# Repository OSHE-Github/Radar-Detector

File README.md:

# Radar-Detector

## Project Details
#### a fully open-source radar detector that can be easily replicated by others. Unlike existing commercial solutions, which are proprietary, this design will provide transparency, customization, and accessibility to users. By creating the first truly open-source radar detector, the project expands available options for individuals interested in building, modifying, or better understanding radar detection technology.
#### This device is powered by the 12V port that's in every commercial vehicle by using a 5V adapter and USB-C connector on board.

## Current State
#### The current Design includes
#### - Completed RF and Control Board
#### - Completed Antenna and Waveguide
#### - A breadboarded circuit for K band detection

## Semester End Report
#### For the Enterprise Program at Michigan Tech there is a end of semester report for the project to summarize the progress of the project. [Link](https://docs.google.com/document/d/1saLg0oObQiK9GF-1CGu6zWZuvDCvK0RMIuFfh2jqqCw/edit?usp=sharing)

## Relevant Standards
#### - Traces Were sized appropriately for current being drawn
#### - No traces can be ran under the main RF lines
#### - There was fusing put in front of the main power input from the USB-C
#### - Decoupling capacitors used to reduce noise from voltage sources going into sensitive components

## Constraints of Design
#### - when working with high frequencies up to 40GHz you have to use special small components that can handle it
#### - The material to make a PCB that can handle that high of frequencies is very expensive
#### - Amplifiers for this frequency are very expensive

## Next Semester Goals
#### - Look into possible cheaper solutions using modules like what we found for the K band
#### - Test the Ka band implementation once we have the antenna
#### - Look into the design on the component for the K band and see if parts of it are re-creatable

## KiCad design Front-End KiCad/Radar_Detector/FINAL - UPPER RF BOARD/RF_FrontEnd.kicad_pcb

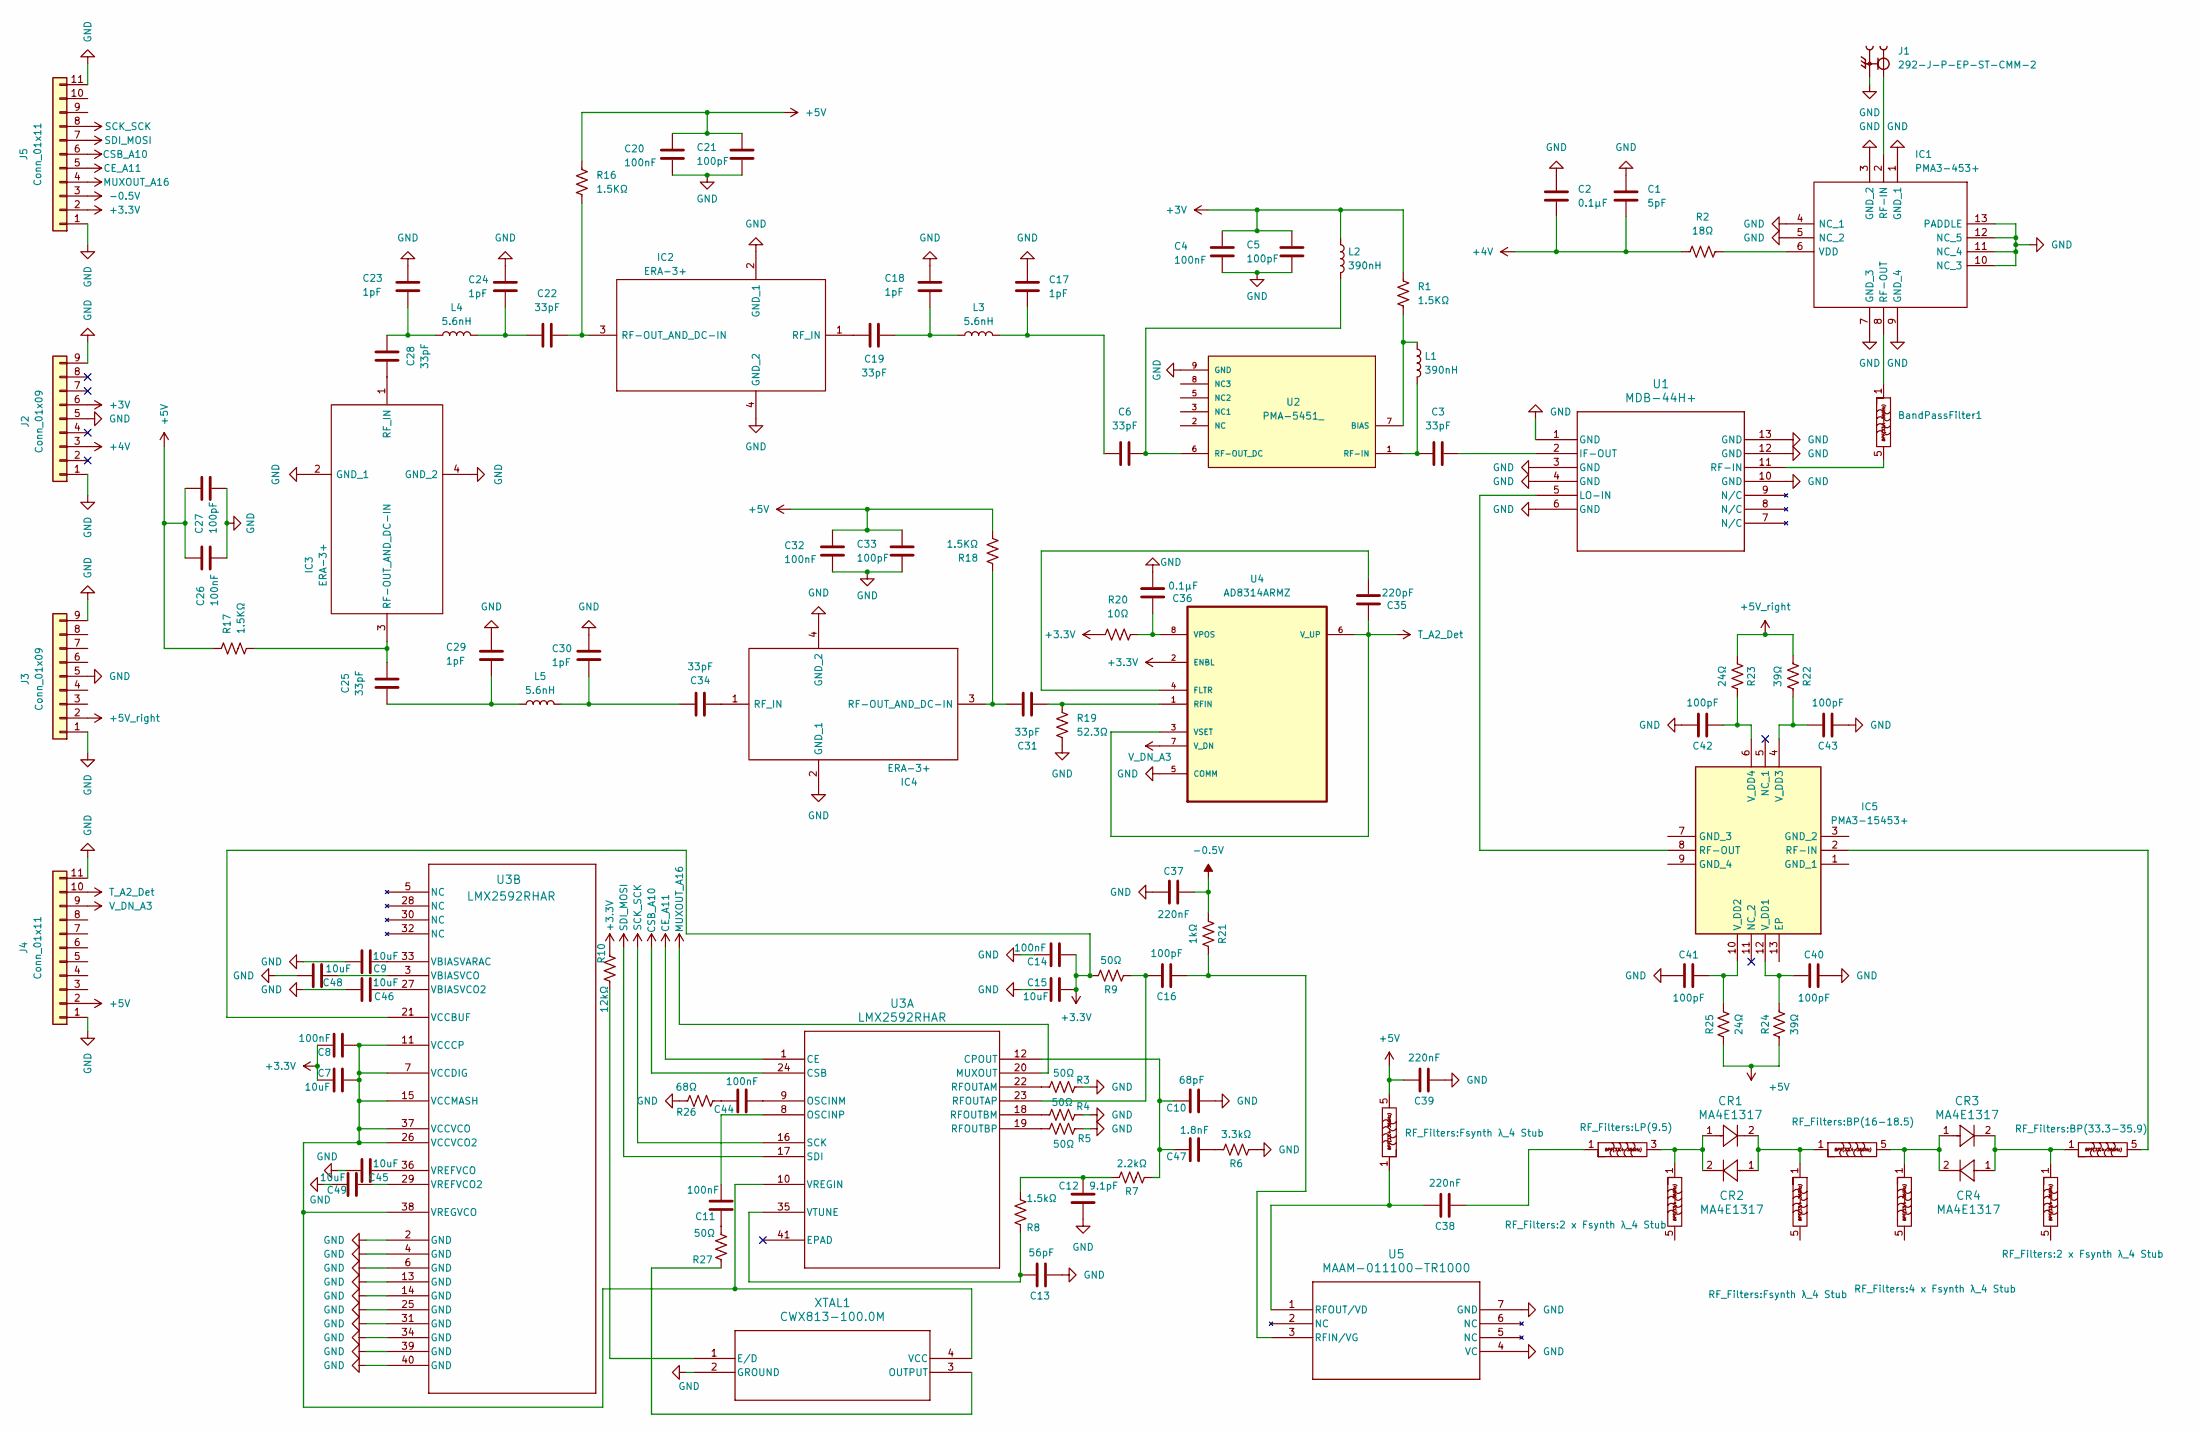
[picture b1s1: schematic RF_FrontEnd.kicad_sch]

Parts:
BandPassFilter1: BP(33.4-36)
BandPassFilter2: 16-18.5 GHz; BP(16-18.5)
BandPassFilter3: 33.3-35.9 GHz; BP(33.3-35.9)
BandPassFilter4: 16-18.5 GHz; LP(9.5)
BandPassFilter5, BandPassFilter7: 16-18.5 GHz; Fsynth λ_4 Stub
BandPassFilter6, BandPassFilter8: 16-18.5 GHz; 2 x Fsynth λ_4 Stub
BandPassFilter9: 16-18.5 GHz; 4 x Fsynth λ_4 Stub
C1: 5pF; C_0402_1005Metric_Pad0.74x0.62mm_HandSolder
C2, C36: 0.1μF; C_0402_1005Metric_Pad0.74x0.62mm_HandSolder
C3, C6, C19, C22, C25, C28, C31, C34: 33pF; C_0402_1005Metric_Pad0.74x0.62mm_HandSolder
C4, C8, C11, C14, C20, C26, C32, C44: 100nF; C_0402_1005Metric_Pad0.74x0.62mm_HandSolder
C5, C16, C21, C27, C33, C40, C41, C42, C43: 100pF; C_0402_1005Metric_Pad0.74x0.62mm_HandSolder
C7, C15: 10uF; C_0805_2012Metric_Pad1.18x1.45mm_HandSolder
C9, C45, C46, C48, C49: 10uF; C_0402_1005Metric_Pad0.74x0.62mm_HandSolder
C10: 68pF; C_0402_1005Metric_Pad0.74x0.62mm_HandSolder
C12: 9.1pF; C_0402_1005Metric_Pad0.74x0.62mm_HandSolder
C13: 56pF; C_0402_1005Metric_Pad0.74x0.62mm_HandSolder
C17, C18, C23, C24, C29, C30: 1pF; C_0402_1005Metric_Pad0.74x0.62mm_HandSolder
C35: 220pF; C_0402_1005Metric_Pad0.74x0.62mm_HandSolder
C37, C39: 220nF; C_0402_1005Metric_Pad0.74x0.62mm_HandSolder
C38: 220nF; C_0201_0603Metric_Pad0.64x0.40mm_HandSolder
C47: 1.8nF; C_0402_1005Metric_Pad0.74x0.62mm_HandSolder
CR1, CR2, CR3, CR4: MA4E1317; MA4E1317_1278_MCM
IC1: PMA3-453+; QFN51P300X300X89-13N; Manufacturer_Part_Number PMA3-453+; Mouser Part Number 139-PMA3-453+
IC2, IC3, IC4: ERA-3+; ERA3; Manufacturer_Part_Number ERA-3+; Mouser Part Number 139-ERA-3
IC5: PMA3-15453+; PMA315453; Mouser Part Number 139-PMA3-15453+
J1: 292-J-P-EP-ST-CMM-2; SAMTEC_292-J-P-EP-ST-CMM-2; PARTREV F
J2, J3: Conn_01x09; PinHeader_1x09_P2.54mm_Vertical
J4, J5: Conn_01x11; PinHeader_1x11_P2.54mm_Vertical
L1, L2: 390nH; L_0603_1608Metric_Pad1.05x0.95mm_HandSolder
L3, L4, L5: 5.6nH; L_0402_1005Metric_Pad0.77x0.64mm_HandSolder
R1: 1.5KΩ; R_0402_1005Metric_Pad0.72x0.64mm_HandSolder
R2: 18Ω; R_0603_1608Metric_Pad0.98x0.95mm_HandSolder
R3, R4, R5: 50Ω; R_0603_1608Metric_Pad0.98x0.95mm_HandSolder
R6: 3.3kΩ; R_0402_1005Metric_Pad0.72x0.64mm_HandSolder
R7: 2.2kΩ; R_0402_1005Metric_Pad0.72x0.64mm_HandSolder
R8: 1.5kΩ; R_0402_1005Metric_Pad0.72x0.64mm_HandSolder
R9, R27: 50Ω; R_0402_1005Metric_Pad0.72x0.64mm_HandSolder
R10: 12kΩ; R_0402_1005Metric_Pad0.72x0.64mm_HandSolder
R16, R17, R18: 1.5KΩ; R_0603_1608Metric_Pad0.98x0.95mm_HandSolder
R19: 52.3Ω; R_0402_1005Metric_Pad0.72x0.64mm_HandSolder
R20: 10Ω; R_0402_1005Metric_Pad0.72x0.64mm_HandSolder
R21: 1kΩ; R_0402_1005Metric_Pad0.72x0.64mm_HandSolder
R22, R24: 39Ω; R_0603_1608Metric_Pad0.98x0.95mm_HandSolder
R23, R25: 24Ω; R_0603_1608Metric_Pad0.98x0.95mm_HandSolder
R26: 68Ω; R_0402_1005Metric_Pad0.72x0.64mm_HandSolder
U1: MDB-44H+; DQ1225_MNC
U2: PMA-5451_; QFN66P300X300X99-9N; PARTREV M
U3: LMX2592RHAR; RHA40_TEX
U4: AD8314ARMZ; SOP65P490X110-8N; MPN AD8314ARMZ
U5: MAAM-011100-TR1000; TDFN6_1.5X1.2_MCM
XTAL1: CWX813-100.0M; CWX813-100.0M_CNW

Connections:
+3.3V: C7.1, C8.1, C14.2, C15.2, J5.2, R9.2, R10.1, R20.2, U3.21 (VCCBUF), U4.2 (ENBL)
+3V: C4.1, C5.1, J2.6, L2.1, R1.2
+4V: C1.2, C2.2, J2.3, R2.1
+5V: BandPassFilter5.5, C20.1, C21.1, C26.1, C27.1, C32.1, C33.1, C39.1, J4.2, R16.2, R17.2, R18.1, R24.1, R25.1
+5V_right: J3.2, R22.1, R23.1
-0.5V: C37.1, J5.3, R21.1
CE_A11: J5.5, U3.1 (CE)
CSB_A10: J5.6, U3.24 (CSB)
GND: C1.1, C2.1, C4.2, C5.2, C9.2, C10.2, C12.2, C13.2, C14.1, C15.1, C17.2, C18.2, C20.2, C21.2, C23.2, C24.2, C26.2, C27.2, C29.2, C30.2, C32.2, C33.2, C36.2, C37.2, C39.2, C40.1, C41.2, C42.1, C43.2, C45.2, C46.2, C48.1, C49.1, IC1.1 (GND_1), IC1.3 (GND_2), IC1.4 (NC_1), IC1.5 (NC_2), IC1.7 (GND_3), IC1.9 (GND_4), IC1.10 (NC_3), IC1.11 (NC_4), IC1.12 (NC_5), IC1.13 (PADDLE), IC2.2 (GND_1), IC2.4 (GND_2), IC3.2 (GND_1), IC3.4 (GND_2), IC4.2 (GND_1), IC4.4 (GND_2), J1.G1, J2.1, J2.5, J2.9, J3.1, J3.5, J3.9, J4.1, J4.11, J5.1, J5.11, R3.1, R4.1, R5.1, R6.1, R19.1, R26.2, U1.1 (GND), U1.3 (GND), U1.4 (GND), U1.6 (GND), U1.10 (GND), U1.12 (GND), U1.13 (GND), U2.9 (GND), U3.2 (GND), U3.4 (GND), U3.6 (GND), U3.13 (GND), U3.14 (GND), U3.25 (GND), U3.31 (GND), U3.34 (GND), U3.39 (GND), U3.40 (GND), U3.41 (EPAD), U3.V, U4.5 (COMM), U5.4 (VC), U5.7 (GND), XTAL1.2 (GROUND)
MUXOUT_A16: J5.4, U3.20 (MUXOUT)
unnamed: BandPassFilter2.1, BandPassFilter7.1, CR1.2, CR2.1
unnamed: BandPassFilter2.5, BandPassFilter9.1, CR3.1, CR4.2
unnamed: BandPassFilter3.1, BandPassFilter8.1, CR3.2, CR4.1
unnamed: BandPassFilter4.1, C38.2
unnamed: BandPassFilter4.3, BandPassFilter6.1, CR1.1, CR2.2
unnamed: C11.2, R27.2
unnamed: C12.1, R7.2, R8.2
unnamed: C6.1, C17.1, L3.2
unnamed: C18.1, C19.2, L3.1
unnamed: C22.1, C24.1, L4.2
unnamed: C23.1, C28.2, L4.1
unnamed: C25.1, C29.1, L5.1
unnamed: C30.1, C34.2, L5.2
unnamed: C44.2, R26.1
unnamed: C47.2, R6.2
unnamed: IC1.2 (RF-IN), J1.1
unnamed: BandPassFilter1.1, IC1.8 (RF-OUT)
unnamed: IC1.6 (VDD), R2.2
unnamed: C22.2, IC2.3 (RF-OUT_AND_DC-IN), R16.1
unnamed: C19.1, IC2.1 (RF_IN)
unnamed: C25.2, IC3.3 (RF-OUT_AND_DC-IN), R17.1
unnamed: C28.1, IC3.1 (RF_IN)
unnamed: C31.2, IC4.3 (RF-OUT_AND_DC-IN), R18.2
unnamed: C34.1, IC4.1 (RF_IN)
unnamed: BandPassFilter3.5, IC5.2 (RF-IN)
unnamed: IC5.8 (RF-OUT), U1.5 (LO-IN)
unnamed: C40.2, IC5.12 (V_DD1), R24.2
unnamed: C41.1, IC5.10 (V_DD2), R25.2
unnamed: C43.1, IC5.4 (V_DD3), R22.2
unnamed: C42.2, IC5.6 (V_DD4), R23.2
unnamed: C3.2, U1.2 (IF-OUT)
unnamed: BandPassFilter1.5, U1.11 (RF-IN)
unnamed: L1.1, R1.1, U2.7 (BIAS)
unnamed: U2.3 (NC1), U2.4 (NC1)
unnamed: C3.1, L1.2, U2.1 (RF-IN)
unnamed: C6.2, L2.2, U2.6 (RF-OUT_DC)
unnamed: C10.1, C47.1, R7.1, U3.12 (CPOUT)
unnamed: C44.1, U3.9 (OSCINM)
unnamed: C11.1, U3.8 (OSCINP)
unnamed: R3.2, U3.22 (RFOUTAM)
unnamed: C16.1, R9.1, U3.23 (RFOUTAP)
unnamed: R4.2, U3.18 (RFOUTBM)
unnamed: R5.2, U3.19 (RFOUTBP)
unnamed: C7.2, C8.2, U3.7 (VCCDIG), U3.10 (VREGIN), U3.11 (VCCCP), U3.15 (VCCMASH), U3.26 (VCCVCO2), U3.37 (VCCVCO), U3.38 (VREGVCO), XTAL1.4 (VCC)
unnamed: C13.1, R8.1, U3.35 (VTUNE)
unnamed: C9.1, U3.33 (VBIASVARAC)
unnamed: C46.1, U3.27 (VBIASVCO2)
unnamed: C48.2, U3.3 (VBIASVCO)
unnamed: C49.2, U3.29 (VREFVCO2)
unnamed: C45.1, U3.36 (VREFVCO)
unnamed: C35.2, U4.4 (FLTR)
unnamed: C31.1, R19.2, U4.1 (RFIN)
unnamed: C36.1, R20.1, U4.8 (VPOS)
unnamed: C16.2, R21.2, U5.3 (RFIN/VG)
unnamed: BandPassFilter5.1, C38.1, U5.1 (RFOUT/VD)
unnamed: R10.2, XTAL1.1 (E/D)
unnamed: R27.1, XTAL1.3 (OUTPUT)
SCK_SCK: J5.8, U3.16 (SCK)
SDI_MOSI: J5.7, U3.17 (SDI)
T_A2_Det: C35.1, J4.10, U4.3 (VSET), U4.6 (V_UP)
V_DN_A3: J4.9, U4.7 (V_DN)

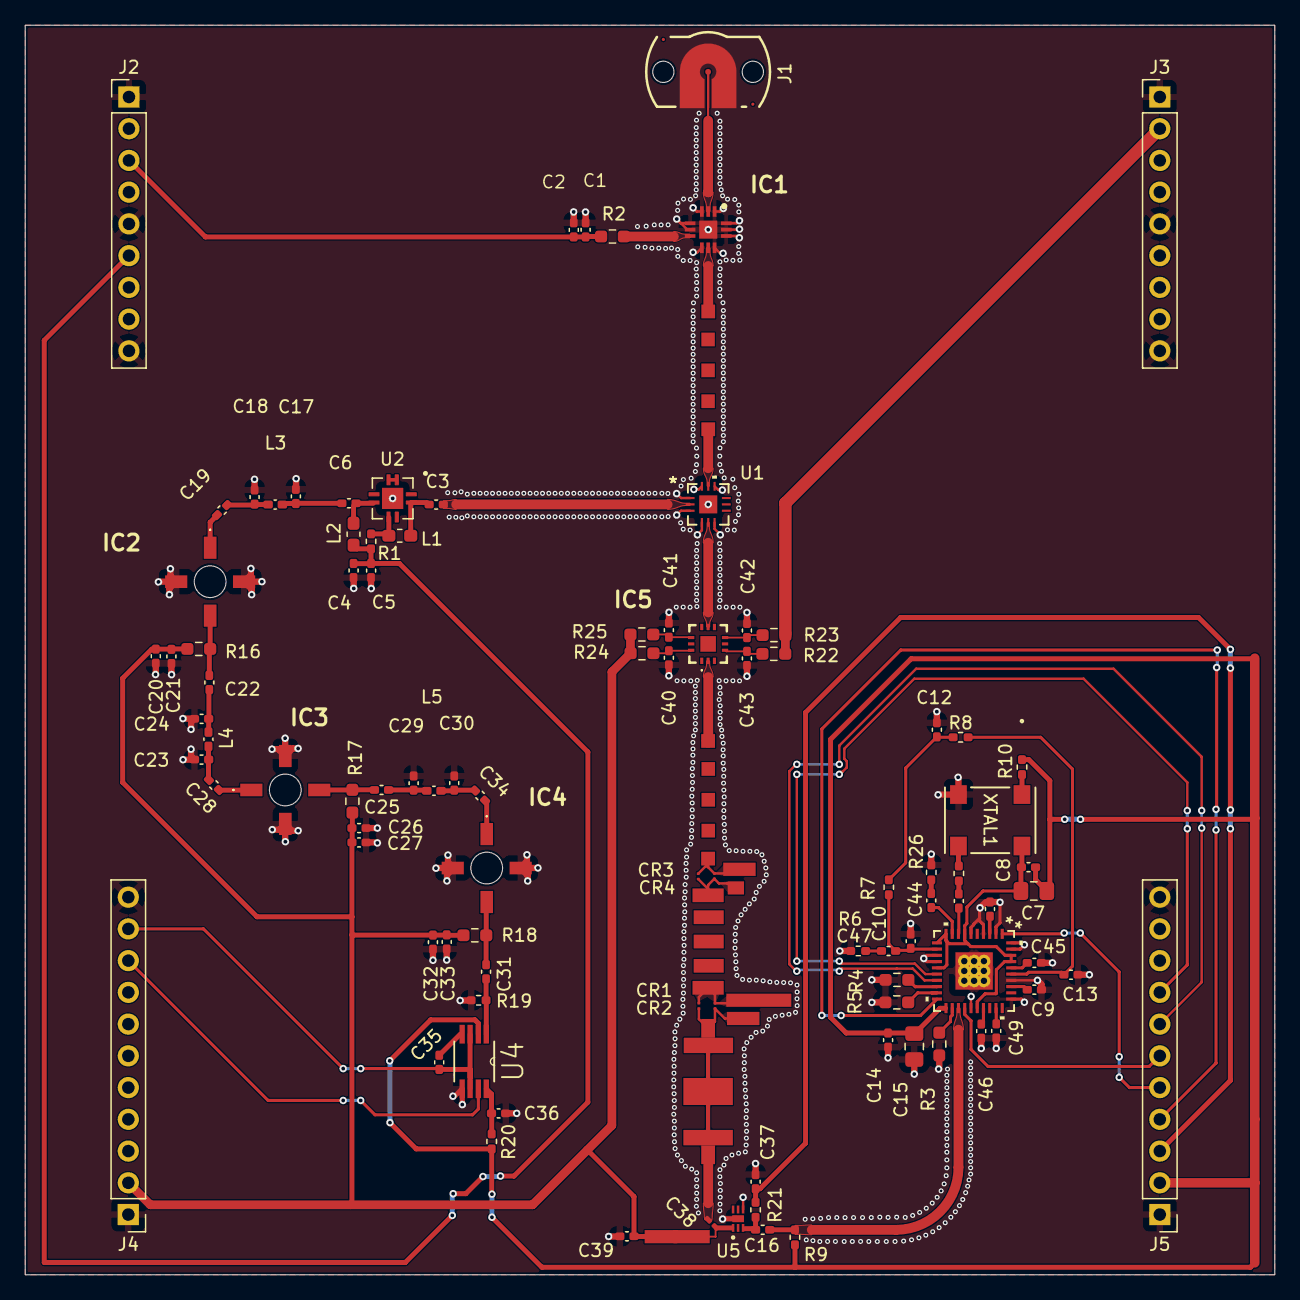
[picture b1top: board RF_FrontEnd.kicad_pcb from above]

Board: 2 copper layers, 100.0 x 100.0 mm, 105 parts (0 on the bottom side), 71 nets.

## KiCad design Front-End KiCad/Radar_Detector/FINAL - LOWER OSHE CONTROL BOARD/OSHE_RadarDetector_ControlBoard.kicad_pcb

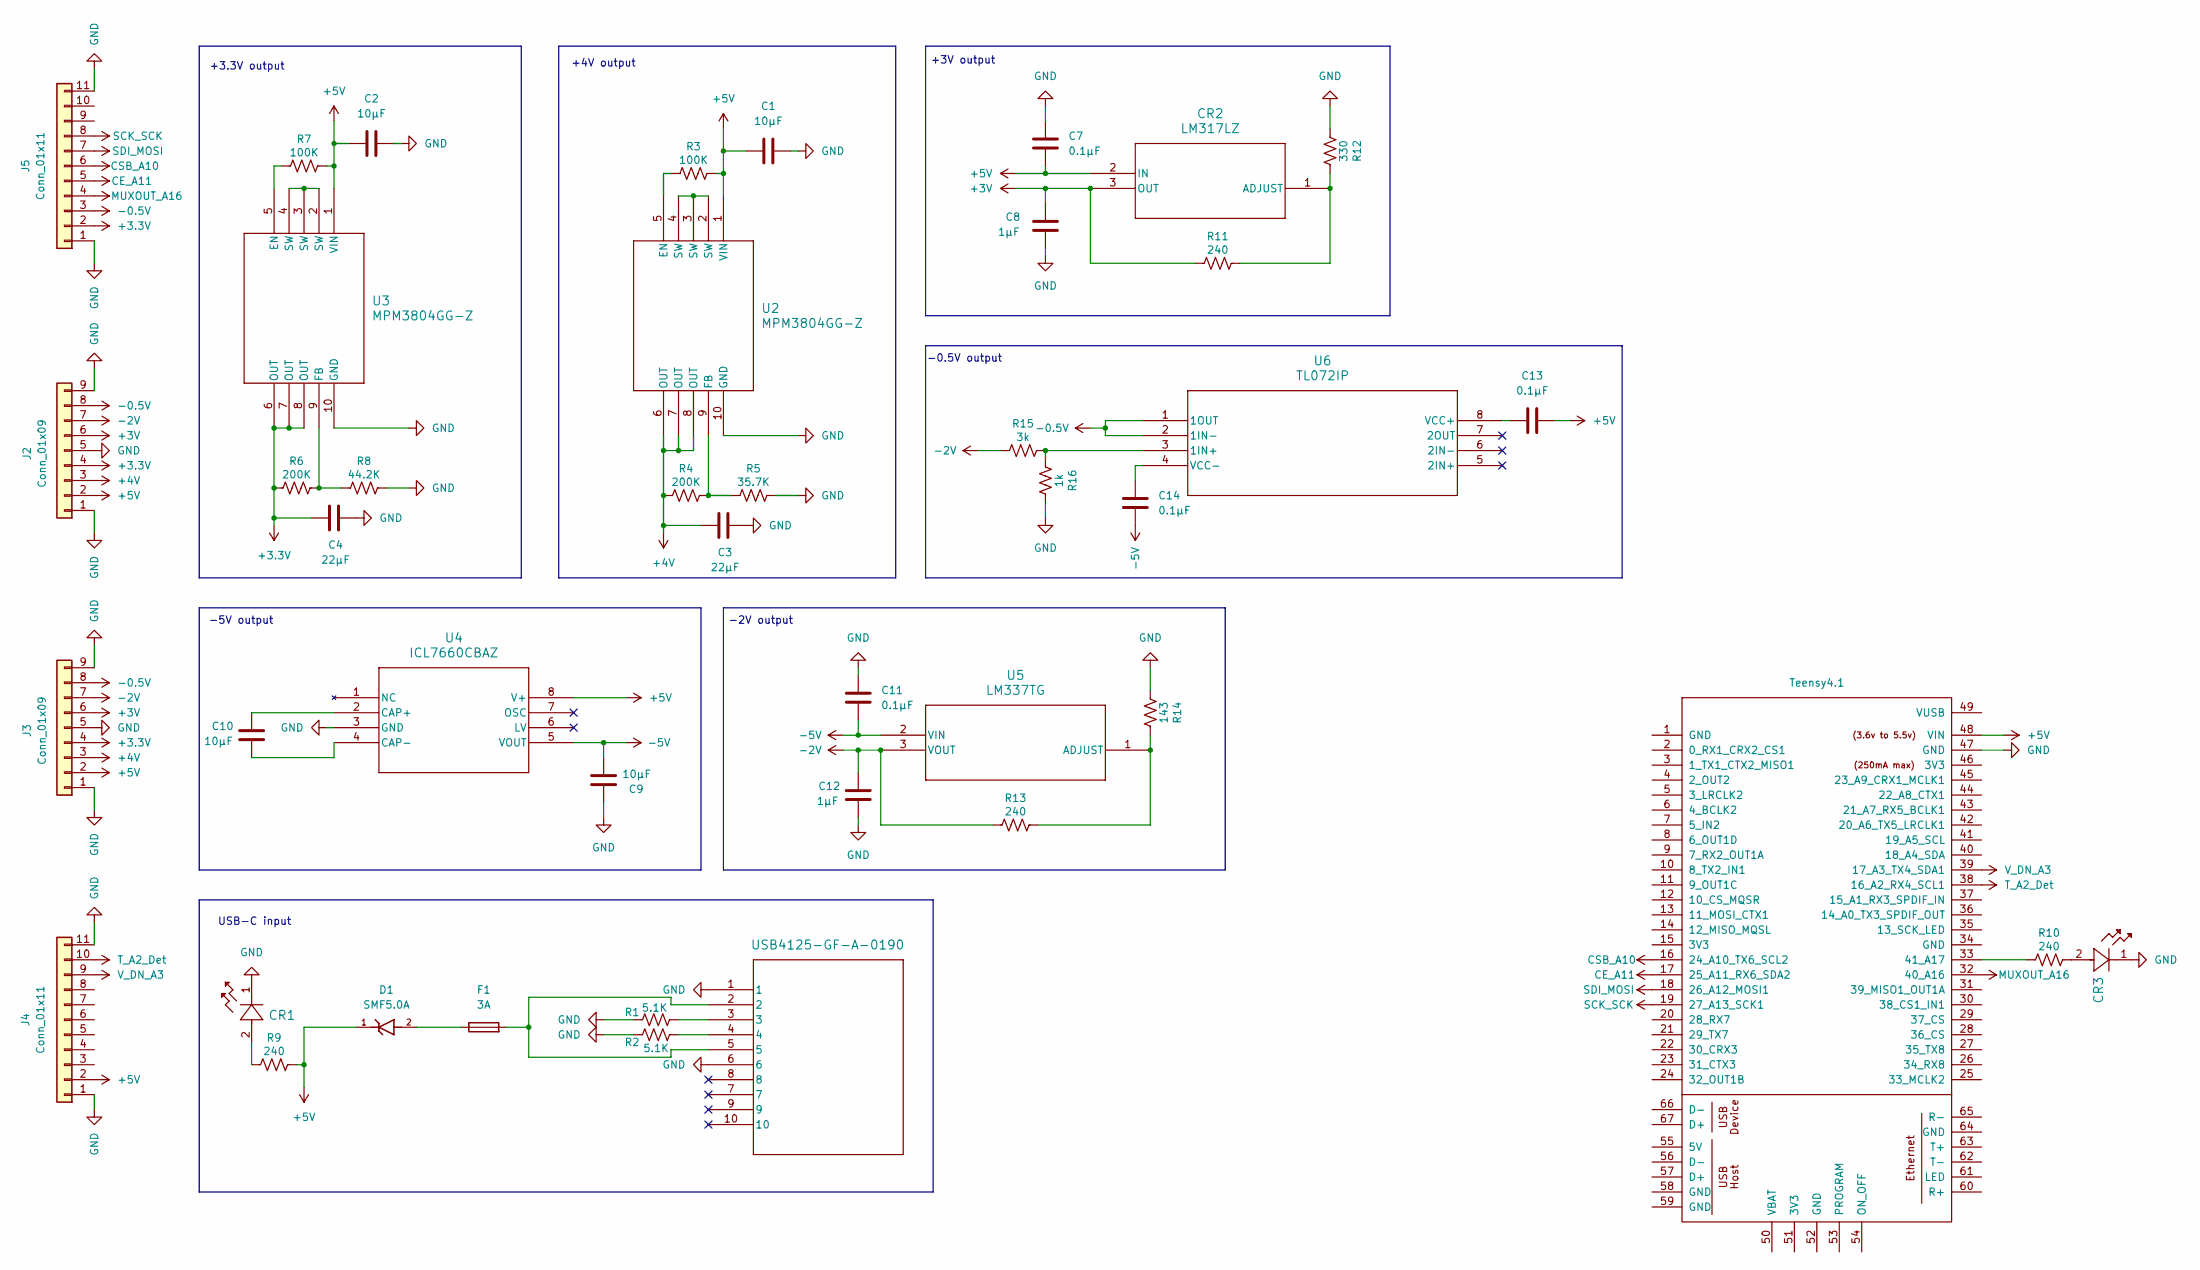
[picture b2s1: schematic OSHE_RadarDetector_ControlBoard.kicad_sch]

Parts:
C1, C2: 10μF; C_0603_1608Metric_Pad1.08x0.95mm_HandSolder
C3, C4: 22μF; C_0805_2012Metric_Pad1.18x1.45mm_HandSolder
C7, C11, C13, C14: 0.1μF; CP_Radial_D5.0mm_P2.50mm
C8, C12: 1μF; CP_Radial_D5.0mm_P2.50mm
C9, C10: 10μF; CP_Radial_D5.0mm_P2.50mm
CR1, CR3: C503B-GCN-CY0C0791; C503B
CR2: LM317LZ; TO-92_STM
D1: SMF5.0A; TVS_SMF5.0A; PARTREV JC
F1: 3A; Fuse_0603_1608Metric_Pad1.05x0.95mm_HandSolder
J1: USB4125-GF-A-0190; CONN6_125-GF-A-0190_GCT
J2, J3: Conn_01x09; PinHeader_1x09_P2.54mm_Vertical
J4, J5: Conn_01x11; PinHeader_1x11_P2.54mm_Vertical
R1, R2: 5.1K; R_0603_1608Metric_Pad0.98x0.95mm_HandSolder
R3, R7: 100K; R_1206_3216Metric_Pad1.30x1.75mm_HandSolder
R4, R6: 200K; R_1206_3216Metric_Pad1.30x1.75mm_HandSolder
R5: 35.7K; R_1206_3216Metric_Pad1.30x1.75mm_HandSolder
R8: 44.2K; R_1206_3216Metric_Pad1.30x1.75mm_HandSolder
R9, R10, R11, R13: 240; R_Axial_DIN0207_L6.3mm_D2.5mm_P7.62mm_Horizontal
R12: 330; R_Axial_DIN0207_L6.3mm_D2.5mm_P7.62mm_Horizontal
R14: 143; R_Axial_DIN0207_L6.3mm_D2.5mm_P7.62mm_Horizontal
R15: 3k; R_Axial_DIN0207_L6.3mm_D2.5mm_P7.62mm_Horizontal
R16: 1k; R_Axial_DIN0207_L6.3mm_D2.5mm_P7.62mm_Horizontal
U1: Teensy4.1; Teensy41
U2, U3: MPM3804GG-Z; QFN2p0x2p0x0p9_MNP
U4: ICL7660CBAZ; SOIC8_4X5_INR
U5: LM337TG; TO220AB-3_ONS
U6: TL072IP; P8

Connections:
+3.3V: C4.1, J2.4, J3.4, J5.2, R6.1, U3.6 (OUT), U3.7 (OUT), U3.8 (OUT); also elsewhere on the board
+3V: C8.2, CR2.3 (OUT), J2.6, J3.6, R11.1; also elsewhere on the board
+4V: C3.1, J2.3, J3.3, R4.1, U2.6 (OUT), U2.7 (OUT), U2.8 (OUT); also elsewhere on the board
+5V: C1.1, C2.1, C7.1, C13.1, CR2.2 (IN), D1.1, J2.2, J3.2, J4.2, R3.2, R7.2, R9.2, U1.48 (VIN), U2.1 (VIN), U3.1 (VIN), U4.8 (V+); also elsewhere on the board
-0.5V: J2.8, J3.8, J5.3, U6.1 (1OUT), U6.2 (1IN-); also elsewhere on the board
-2V: C12.2, J2.7, J3.7, R13.1, R15.1, U5.3 (VOUT); also elsewhere on the board
-5V: C9.1, C11.1, C14.2, U4.5 (VOUT), U5.2 (VIN)
CE_A11: J5.5, U1.17 (25_A11_RX6_SDA2)
CSB_A10: J5.6, U1.16 (24_A10_TX6_SCL2)
GND: C1.2, C2.2, C3.2, C4.2, C7.2, C8.1, C9.2, C11.2, C12.1, CR1.1, CR3.1, J1.1, J1.6, J2.1, J2.5, J2.9, J3.1, J3.5, J3.9, J4.1, J4.11, J5.1, J5.11, R1.1, R2.1, R5.2, R8.2, R12.1, R14.1, R16.2, U1.47 (GND), U2.10 (GND), U3.10 (GND), U4.3 (GND); also elsewhere on the board
MUXOUT_A16: J5.4, U1.32 (40_A16)
unnamed: CR1.2, R9.1
unnamed: CR2.1 (ADJUST), R11.2, R12.2
unnamed: CR3.2, R10.2
unnamed: D1.2, F1.1
unnamed: F1.2, J1.2, J1.5
unnamed: J1.3, R1.2
unnamed: J1.4, R2.2
unnamed: R10.1, U1.33 (41_A17)
unnamed: R3.1, U2.5 (EN)
unnamed: R4.2, R5.1, U2.9 (FB)
unnamed: U2.2 (SW), U2.3 (SW), U2.4 (SW)
unnamed: R7.1, U3.5 (EN)
unnamed: R6.2, R8.1, U3.9 (FB)
unnamed: U3.2 (SW), U3.3 (SW), U3.4 (SW)
unnamed: C10.2, U4.2 (CAP+)
unnamed: C10.1, U4.4 (CAP-)
unnamed: R13.2, R14.2, U5.1 (ADJUST)
unnamed: R15.2, R16.1, U6.3 (1IN+)
unnamed: C13.2, U6.8 (VCC+)
unnamed: C14.1, U6.4 (VCC-)
SCK_SCK: J5.8, U1.19 (27_A13_SCK1)
SDI_MOSI: J5.7, U1.18 (26_A12_MOSI1)
T_A2_Det: J4.10, U1.38 (16_A2_RX4_SCL1)
V_DN_A3: J4.9, U1.39 (17_A3_TX4_SDA1)

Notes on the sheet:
-2V output
-0.5V output
+3V output
+3.3V output
-5V output
+4V output
USB-C input

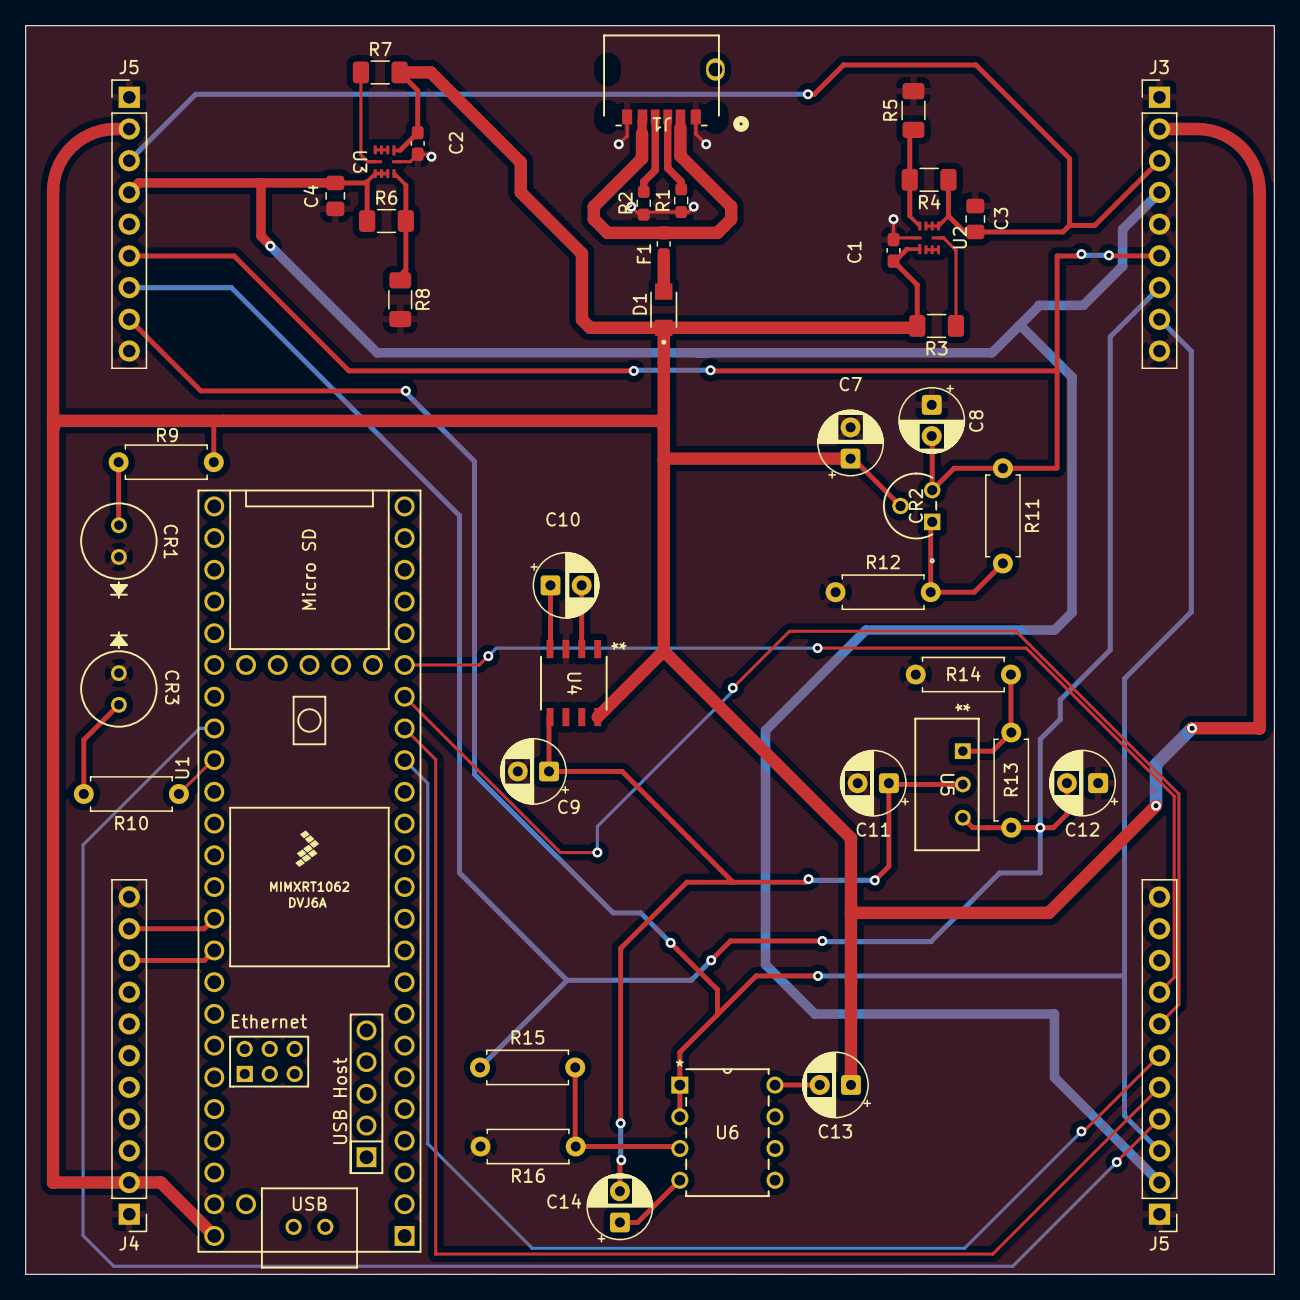
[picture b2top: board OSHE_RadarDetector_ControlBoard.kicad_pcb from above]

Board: 2 copper layers, 100.0 x 100.0 mm, 44 parts (0 on the bottom side), 35 nets.

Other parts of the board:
J5#2: Conn_01x09; PinHeader_1x09_P2.54mm_Vertical

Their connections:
+3.3V: J5#2.4; also elsewhere on the board
+3V: J5#2.6; also elsewhere on the board
+4V: J5#2.3; also elsewhere on the board
+5V: J5#2.2; also elsewhere on the board
-0.5V: J5#2.8; also elsewhere on the board
-2V: J5#2.7; also elsewhere on the board
GND: J5#2.1, J5#2.9; also elsewhere on the board

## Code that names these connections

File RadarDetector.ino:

//Includes
#include <SPI.h>

//Detector to Microcontroller connections
int Detector_V_UP = 16; // Analog value from 0-1V based on strength of signal detected
int Detector_V_DN = 17; // inverse V_UP signal so 1-0V based on signal strength detected

//Synthesizer to Microcontroller connections
int CSB_A10  = 24;
int CE_A11   = 25;
int SDI_MOSI = 26;
int SCK_SCK  = 27;
int Muxout   = 40;

//Microcontroller to LED
int LED_RED = 41;

void setup() 
{
  pinMode(LED_RED, OUTPUT);

  Serial.begin(115200);

  // AD8314 analog inputs
  pinMode(Detector_V_UP, INPUT);
  pinMode(Detector_V_DN, INPUT);

  // LMX2592 control pins
  pinMode(CSB_A10, OUTPUT);
  pinMode(CE_A11, OUTPUT);
  pinMode(Muxout, INPUT); // lock condition of synthesizer

  digitalWrite(CSB_A10, HIGH);   // inactive
  digitalWrite(CE_A11, LOW);     // keep synth off until ready

  // SPI1 on Teensy 4.1
  SPI1.setMOSI(SDI_MOSI);
  SPI1.setSCK(SCK_SCK);
  SPI1.begin();

  // Enable synthesizer
  digitalWrite(CE_A11, HIGH);
  delay(10);


}

void loop() 
{
  //start Synthesizer
  digitalWrite(CE_A11, HIGH);

  //main detection section
  float Det_Voltage = analogRead(Detector_V_UP)*(5.0 / 1023.0); // voltage received by Detector
  if(Det_Voltage > 0.05 && Det_Voltage < 0.2)
  {
    //weak signal detected
    digitalWrite(41, LOW);
  }
  if(Det_Voltage > 0.35 && Det_Voltage < 0.5)
  {
    //medium signal detected
    digitalWrite(41, HIGH);
  }
  if(Det_Voltage > 0.5 && Det_Voltage < 1)
  {
    //strong signal detected
    digitalWrite(41, HIGH);
  }



  
}

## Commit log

2026-01-26 Horn Antenna
    Matlab code to generate mesh for horn antenna. Along with instructions to import it into FreeCAD and already created FreeCAD files
2026-01-27 Horn Antenna V2
    Created Horn Antenna V2 and organized Files
2026-02-10 Horn Antenna V3 & Organization
    Organized the folders. Additionally, Created V3; this focuses on the Ka band instead of the previous X through Ka Band.
2026-03-26 Addign files for Evan
    First draft of Teensy code
2026-03-31 Nano-detector
2026-04-23 Update README.md
    This is a test to see what this looks like!
2026-04-23 Finalized Horn Antenna & Waveguide
    Uploaded Final Horn antenna & Waveguide Models along with updating readme and adding documents folder
2026-04-23 Added PCB Files to Github
